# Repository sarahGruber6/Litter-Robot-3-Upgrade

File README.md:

My boyfriend and I got scammed off marketplace buying a broken Litter Robot 3. 
I figured I might as well upgrade it since all the sensors/motors work and it seemed fun.

In this repo I'm creating a replacement control board, as well as an upgrade board to the LED nightlight to have camera support, and replacing the weight switch with a proper load cell. 
The control board will be compatible with all OEM sensors while also having pins for upgraded boards/sensors. 

The end goal is to have this control board be accessible through local wifi to view sensor data and camera feed. I do not look forward to the software side of this. :-D
Feel free to tag along as I develop!

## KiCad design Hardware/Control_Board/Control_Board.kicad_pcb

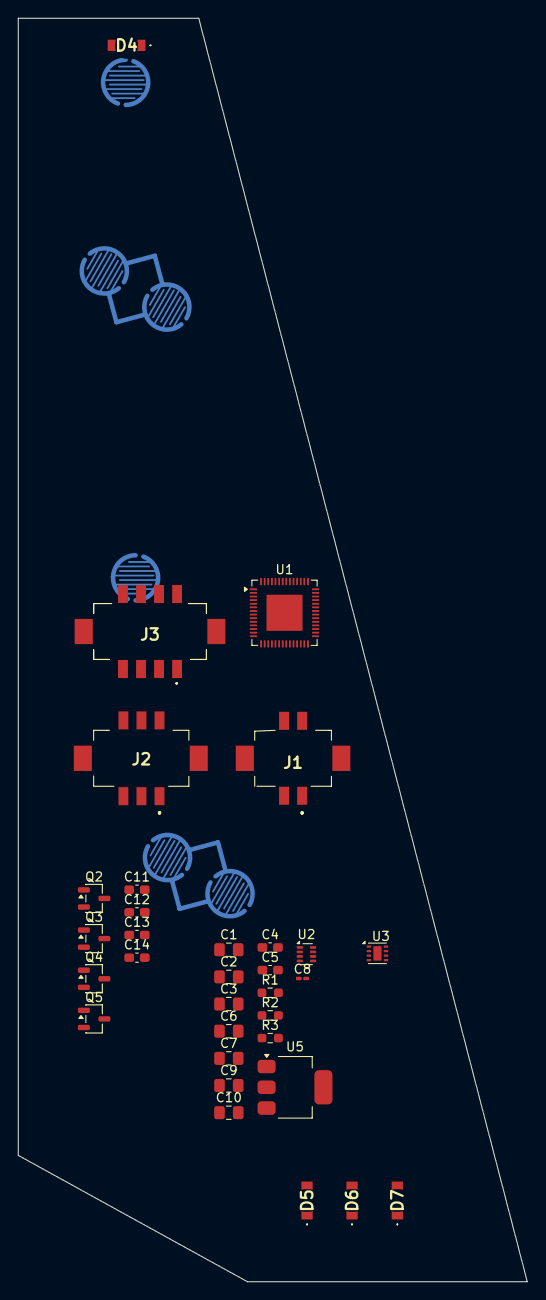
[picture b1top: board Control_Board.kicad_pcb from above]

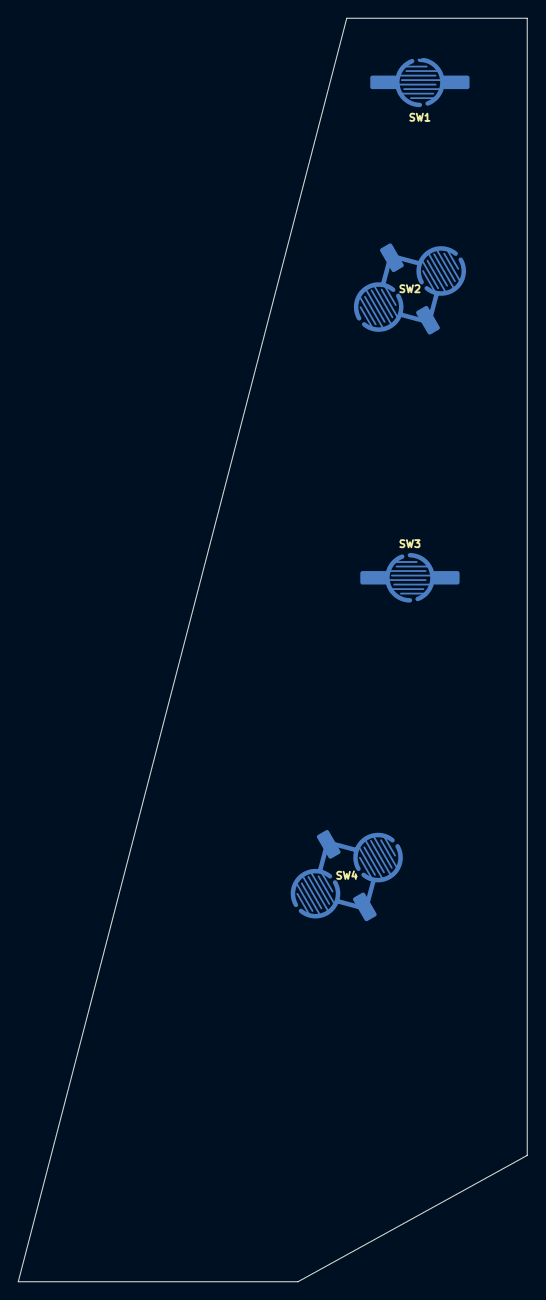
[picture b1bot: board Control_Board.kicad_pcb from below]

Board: 2 copper layers, 56.4 x 140.0 mm, 36 parts (4 on the bottom side), 16 nets, no tracks yet.

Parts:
C1, C2, C3: 10uF; C_0805_2012Metric_Pad1.18x1.45mm_HandSolder
C4: 33nF; C_0603_1608Metric_Pad1.08x0.95mm_HandSolder
C5, C11, C12, C13, C14: 100nF; C_0603_1608Metric_Pad1.08x0.95mm_HandSolder
C6, C7: 22uF; C_0805_2012Metric_Pad1.18x1.45mm_HandSolder
C8: 100nF; C_0201_0603Metric_Pad0.64x0.40mm_HandSolder
C9: 1uF; C_0805_2012Metric_Pad1.18x1.45mm_HandSolder
C10: 2.2uF; C_0805_2012Metric_Pad1.18x1.45mm_HandSolder
D4, D5, D6, D7: LED; LED_1204_Hole
J1: DF11CZ-4DP-2V_27_; DF11CZ4DP2V27
J2: DF11CZ-4DP-2V_27_; DF11CZ6DP2V27
J3: DF11CZ-8DP-2V_27_; DF11CZ8DP2V27
Q2, Q3, Q4, Q5: 2N7002; SOT-23-3
R1: 10k; R_0603_1608Metric_Pad0.98x0.95mm_HandSolder
R2: 52.3k; R_0603_1608Metric_Pad0.98x0.95mm_HandSolder
R3: 51.1k; R_0603_1608Metric_Pad0.98x0.95mm_HandSolder
SW1: Power; Contact_Switch_5mm
SW2: Cycle; Contact_Switch_5mm_Double
SW3: Empty; Contact_Switch_5mm
SW4: Reset; Contact_Switch_5mm_Double
U1: ESP32-S2; QFN-56-1EP_7x7mm_P0.4mm_EP4x4mm
U2: TPS62933; SOT-583-8
U3: DRV8231ADSG; WSON-8-1EP_2x2mm_P0.5mm_EP0.9x1.6mm
U5: TLV76133DCY; SOT-223-3_TabPin2

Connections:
+3.3V: C10.1, U5.2 (VO)
+5V: C6.1, C7.1, C8.1, C9.1, R3.1, U5.3 (VI)
Batt PWR: C1.1, C2.1, C3.1, J2.1, J2.6, U2.2 (EN), U2.3 (VIN)
GND: C1.2, C2.2, C3.2, C4.2, C6.2, C7.2, C8.2, C9.2, C10.2, C11.2, C12.2, C13.2, C14.2, J2.2, J2.4, J3.4, J3.6, J3.8, Q2.2 (S), Q3.2 (S), Q4.2 (S), Q5.2 (S), R1.2, SW1.2, SW2.2, SW3.2, SW4.2, U2.4 (GND), U5.1 (GND)
unnamed: D4.1 (K), Q2.3 (D)
unnamed: D5.1 (K), Q3.3 (D)
unnamed: D6.1 (K), Q4.3 (D)
unnamed: D7.1 (K), Q5.3 (D)
unnamed: R2.2, R3.2
unnamed: U1.3 (VDD3P3), U1.4 (VDD3P3)
unnamed: U1.1 (VDDA), U1.51 (VDDA), U1.54 (VDDA)
unnamed: C5.2, U2.6 (BST)
unnamed: R1.1, R2.1, U2.8 (FB)
unnamed: C4.1, U2.7 (SS)
unnamed: C5.1, U2.5 (SW)
unnamed: U3.7 (GND), U3.9 (GND)

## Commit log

2026-04-19 init, start of schematic and created rough plan outline
2026-04-19 fleshed out info/planning, roughed in more schematics, added short readme
2026-04-25 took measurements, need to make contact switch for silicon footprint
2026-04-26 made contact switch footprints + LED through hole footprints
